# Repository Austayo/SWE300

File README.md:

# SWE300
Silicon Wolf Embedded 300

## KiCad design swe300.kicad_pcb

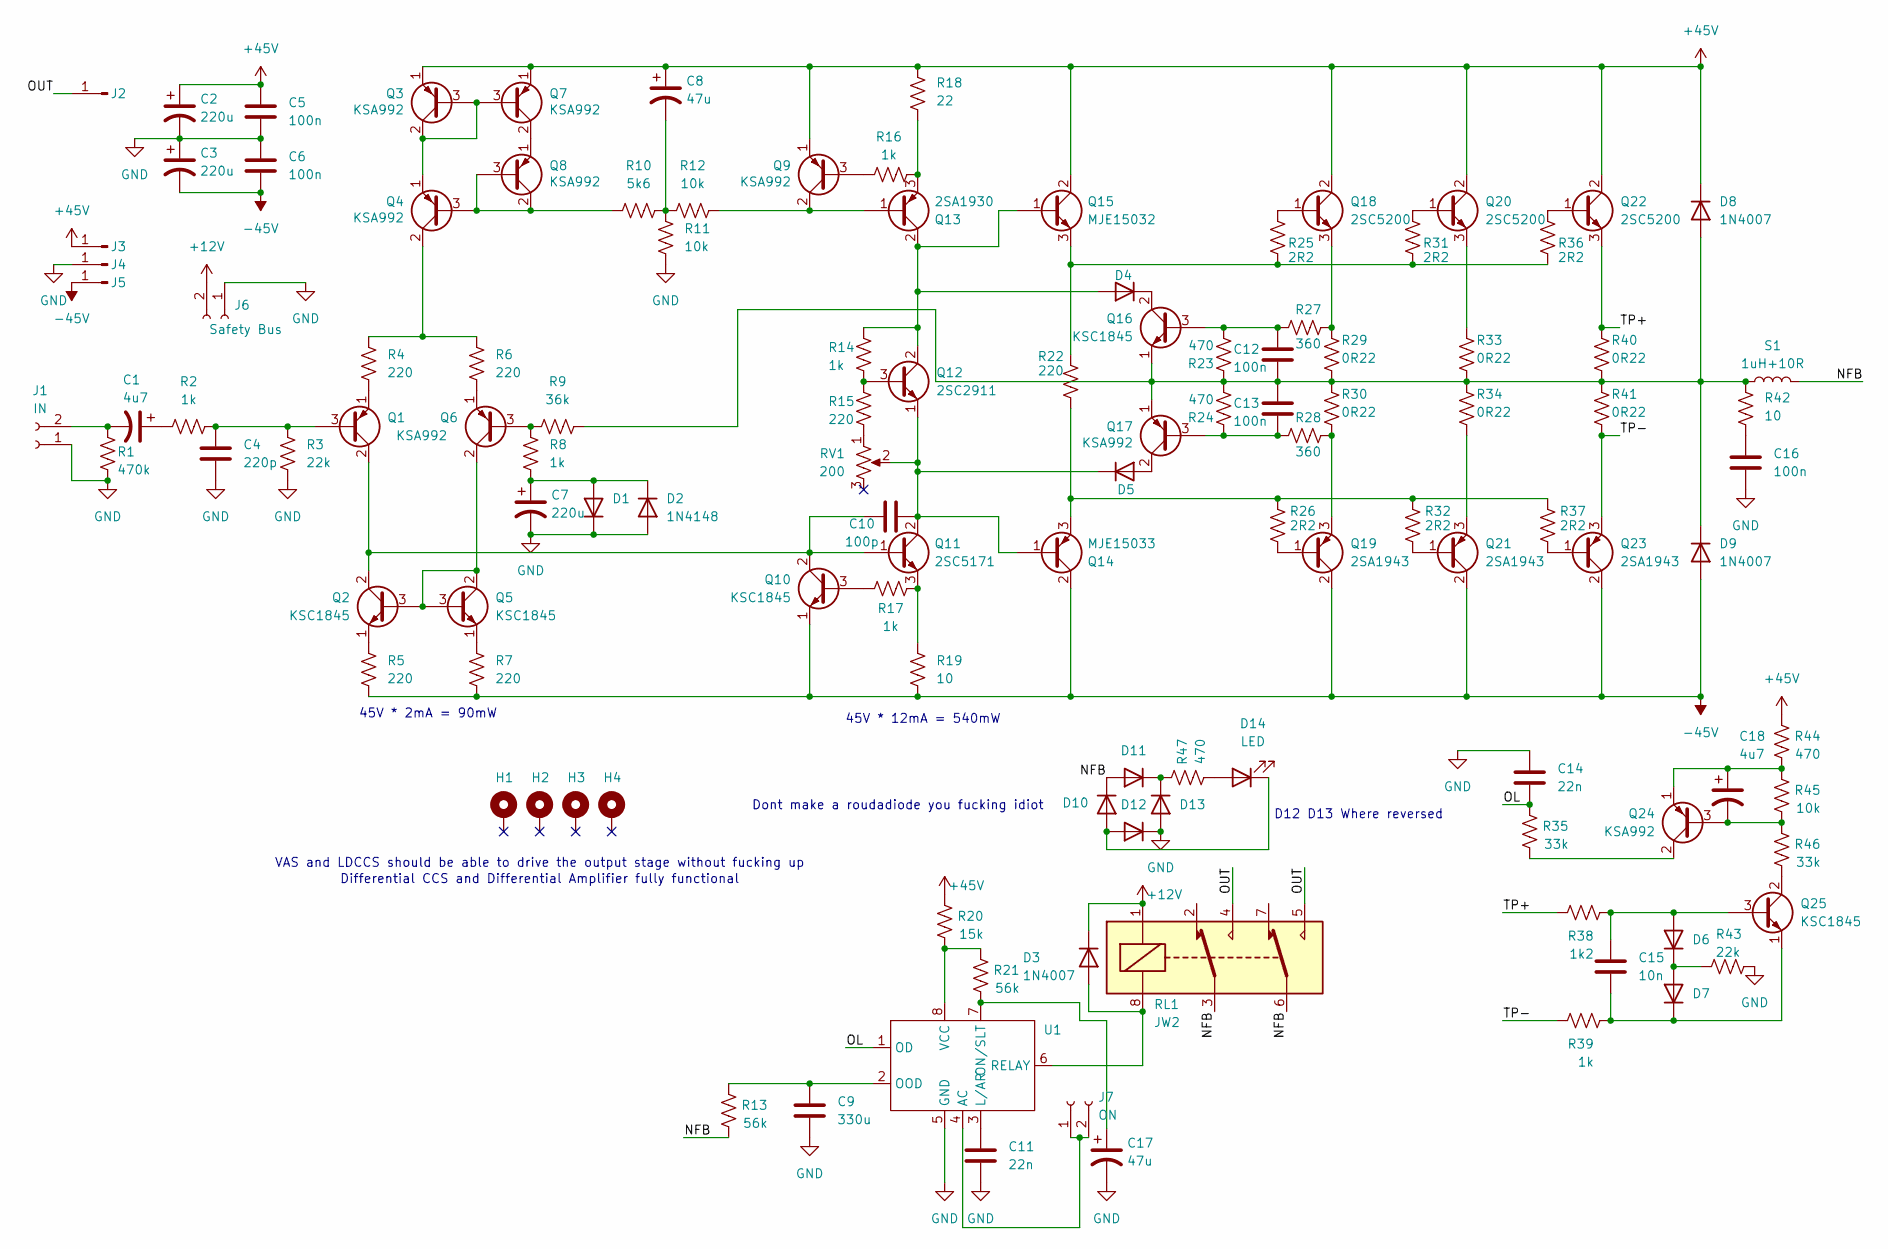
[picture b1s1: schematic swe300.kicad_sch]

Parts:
C1, C18: 4u7; CP_Radial_D6.3mm_P2.50mm
C2, C3: 220u; CP_Radial_D10.0mm_P5.00mm
C4: 220p; C_Disc_D4.7mm_W2.5mm_P5.00mm
C5, C6, C12, C13, C16: 100n; C_Rect_L7.0mm_W2.0mm_P5.00mm
C7: 220u; CP_Radial_D6.3mm_P2.50mm
C8, C17: 47u; CP_Radial_D6.3mm_P2.50mm
C9: 330u; C_Radial_D8.0mm_H11.5mm_P3.50mm
C10: 100p; C_Disc_D4.7mm_W2.5mm_P5.00mm
C11, C14: 22n; C_Rect_L7.0mm_W2.0mm_P5.00mm
C15: 10n; C_Rect_L7.0mm_W2.0mm_P5.00mm
D1, D2, D4, D5, D6, D7, D10, D11, D12, D13: 1N4148; D_DO-35_SOD27_P7.62mm_Horizontal
D3, D8, D9: 1N4007; D_DO-41_SOD81_P10.16mm_Horizontal
D14: LED; LED_D4.0mm
H1, H2, H3, H4: MountingHole_Pad; MountingHole_3.2mm_M3_DIN965_Pad_TopBottom
J1: IN; PinHeader_1x02_P2.54mm_Vertical
J2, J3, J4, J5: 6.3mm spade
J6: Safety Bus; PinHeader_1x02_P2.54mm_Vertical
J7: ON; PinHeader_1x02_P2.54mm_Vertical
Q1, Q3, Q4, Q6, Q7, Q8, Q9, Q17, Q24: KSA992; TO-92L_Inline_Wide
Q2, Q5, Q10, Q16, Q25: KSC1845; TO-92L_Inline_Wide
Q11: 2SC5171; TO-220-3_Vertical
Q12: 2SC2911; TO-126-3_Horizontal_TabUp
Q13: 2SA1930; TO-220-3_Vertical
Q14: MJE15033; TO-220-3_Horizontal_TabUp
Q15: MJE15032; TO-220-3_Horizontal_TabUp
Q18, Q20, Q22: 2SC5200; TO-264-3_Horizontal_TabUp
Q19, Q21, Q23: 2SA1943; TO-264-3_Horizontal_TabUp
R1: 470k; R_Axial_DIN0207_L6.3mm_D2.5mm_P10.16mm_Horizontal
R2, R8, R14, R16, R17, R39: 1k; R_Axial_DIN0207_L6.3mm_D2.5mm_P10.16mm_Horizontal
R3, R43: 22k; R_Axial_DIN0207_L6.3mm_D2.5mm_P10.16mm_Horizontal
R4, R5, R6, R7, R15, R22: 220; R_Axial_DIN0207_L6.3mm_D2.5mm_P10.16mm_Horizontal
R9: 36k; R_Axial_DIN0207_L6.3mm_D2.5mm_P10.16mm_Horizontal
R10: 5k6; R_Axial_DIN0207_L6.3mm_D2.5mm_P10.16mm_Horizontal
R11, R12, R45: 10k; R_Axial_DIN0207_L6.3mm_D2.5mm_P10.16mm_Horizontal
R13, R21: 56k; R_Axial_DIN0207_L6.3mm_D2.5mm_P10.16mm_Horizontal
R18: 22; R_Axial_DIN0207_L6.3mm_D2.5mm_P10.16mm_Horizontal
R19: 10; R_Axial_DIN0207_L6.3mm_D2.5mm_P10.16mm_Horizontal
R20: 15k; R_Axial_DIN0207_L6.3mm_D2.5mm_P10.16mm_Horizontal
R23, R24, R44, R47: 470; R_Axial_DIN0207_L6.3mm_D2.5mm_P10.16mm_Horizontal
R25, R26, R31, R32, R36, R37: 2R2; R_Axial_DIN0207_L6.3mm_D2.5mm_P10.16mm_Horizontal
R27, R28: 360; R_Axial_DIN0207_L6.3mm_D2.5mm_P10.16mm_Horizontal
R29, R30, R33, R34, R40, R41: 0R22; R_Axial_DIN0922_L20.0mm_D9.0mm_P25.40mm_Horizontal
R35, R46: 33k; R_Axial_DIN0207_L6.3mm_D2.5mm_P10.16mm_Horizontal
R38: 1k2; R_Axial_DIN0207_L6.3mm_D2.5mm_P10.16mm_Horizontal
R42: 10; R_Axial_DIN0309_L9.0mm_D3.2mm_P12.70mm_Horizontal
RL1: JW2; Relay_DPDT_Panasonic_JW2
RV1: 200; Potentiometer_Runtron_RM-063_Horizontal
S1: 1uH+10R; 10mm Snubber
U1: SIP-8_19x3mm_P2.54mm

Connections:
+12V: D3.1 (K), J6.2, RL1.1
+45V: C2.1, C5.1, C8.1, D8.1 (K), J3.1, Q3.1 (E), Q7.1 (E), Q9.1 (E), Q15.2 (C), Q18.2 (C), Q20.2 (C), Q22.2 (C), R18.1, R20.1, R44.1
-45V: C3.2, C6.2, D9.2 (A), J5.1, Q10.1 (E), Q14.2 (C), Q19.2 (C), Q21.2 (C), Q23.2 (C), R5.2, R7.2, R19.2
/NFB: D10.1 (K), D11.2 (A), R13.2, RL1.3, RL1.6, S1.2
/OL: C14.2, R35.1, U1.1 (OD)
/OUT: J2.1, RL1.4, RL1.5
/TP+: Q22.3 (E), R38.2, R40.2
/TP-: Q23.3 (E), R39.2, R41.1
GND: C2.2, C3.1, C4.2, C5.2, C6.1, C7.2, C9.2, C11.2, C14.1, C16.2, C17.2, D1.1 (K), D2.2 (A), D12.1 (K), D13.2 (A), J1.1, J4.1, J6.1, R1.2, R3.1, R11.1, R43.2, U1.5 (GND)
unnamed: C1.1, R2.2
unnamed: C8.2, R10.2, R11.2, R12.2
unnamed: C16.1, R42.2
unnamed: C7.1, D1.2 (A), D2.1 (K), R8.1
unnamed: D3.2 (A), RL1.8, U1.6 (RELAY)
unnamed: D4.2 (A), Q12.2 (C), Q13.2 (C), Q15.1 (B), R14.2
unnamed: D4.1 (K), Q16.2 (C)
unnamed: D5.2 (A), Q17.2 (C)
unnamed: C10.2, D5.1 (K), Q11.2 (C), Q12.1 (E), Q14.1 (B), RV1.2
unnamed: C15.1, D6.2 (A), Q25.3 (B), R38.1
unnamed: D6.1 (K), D7.2 (A), R43.1
unnamed: C15.2, D7.1 (K), Q25.1 (E), R39.1
unnamed: C12.1, C13.2, D8.2 (A), D9.1 (K), Q16.1 (E), Q17.1 (E), R9.1, R23.1, R24.2, R29.1, R30.2, R33.1, R34.2, R40.1, R41.2, R42.1, S1.1
unnamed: D10.2 (A), D12.2 (A), D14.1 (K)
unnamed: D11.1 (K), D13.1 (K), R47.1
unnamed: D14.2 (A), R47.2
unnamed: C1.2, J1.2, R1.1
unnamed: J7.1, J7.2, U1.4 (AC)
unnamed: C4.1, Q1.3 (B), R2.1, R3.2
unnamed: C10.1, Q1.2 (C), Q2.2 (C), Q10.2 (C), Q11.1 (B)
unnamed: Q1.1 (E), R4.2
unnamed: Q2.3 (B), Q5.2 (C), Q5.3 (B), Q6.2 (C)
unnamed: Q2.1 (E), R5.1
unnamed: Q3.2 (C), Q3.3 (B), Q4.1 (E), Q7.3 (B)
unnamed: Q4.3 (B), Q8.2 (C), Q8.3 (B), R10.1
unnamed: Q4.2 (C), R4.1, R6.1
unnamed: Q5.1 (E), R7.1
unnamed: Q6.3 (B), R8.2, R9.2
unnamed: Q6.1 (E), R6.2
unnamed: Q7.2 (C), Q8.1 (E)
unnamed: Q9.3 (B), R16.2
unnamed: Q10.3 (B), R17.1
unnamed: Q11.3 (E), R17.2, R19.1
unnamed: Q12.3 (B), R14.1, R15.2
unnamed: Q9.2 (C), Q13.1 (B), R12.1
unnamed: Q13.3 (E), R16.1, R18.2
unnamed: Q14.3 (E), R22.1, R26.2, R32.2, R37.2
unnamed: Q15.3 (E), R22.2, R25.1, R31.1, R36.1
unnamed: C12.2, Q16.3 (B), R23.2, R27.2
unnamed: C13.1, Q17.3 (B), R24.1, R28.2
unnamed: Q18.1 (B), R25.2
unnamed: Q18.3 (E), R27.1, R29.2
unnamed: Q19.1 (B), R26.1
unnamed: Q19.3 (E), R28.1, R30.1
unnamed: Q20.1 (B), R31.2
unnamed: Q20.3 (E), R33.2
unnamed: Q21.1 (B), R32.1
unnamed: Q21.3 (E), R34.1
unnamed: Q22.1 (B), R36.2
unnamed: Q23.1 (B), R37.1
unnamed: C18.2, Q24.3 (B), R45.2, R46.1
unnamed: Q24.2 (C), R35.2
unnamed: C18.1, Q24.1 (E), R44.2, R45.1
unnamed: Q25.2 (C), R46.2
unnamed: R15.1, RV1.1
unnamed: C11.1, U1.3 (L/AR)
unnamed: C17.1, R21.2, U1.7 (ON/SLT)
unnamed: C9.1, R13.1, U1.2 (OOD)
unnamed: R20.2, R21.1, U1.8 (VCC)

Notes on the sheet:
45V * 12mA = 540mW
D12 D13 Where reversed
VAS and LDCCS should be able to drive the output stage without fucking up
45V * 2mA = 90mW
Dont make a roudadiode you fucking idiot
Differential CCS and Differential Amplifier fully functional

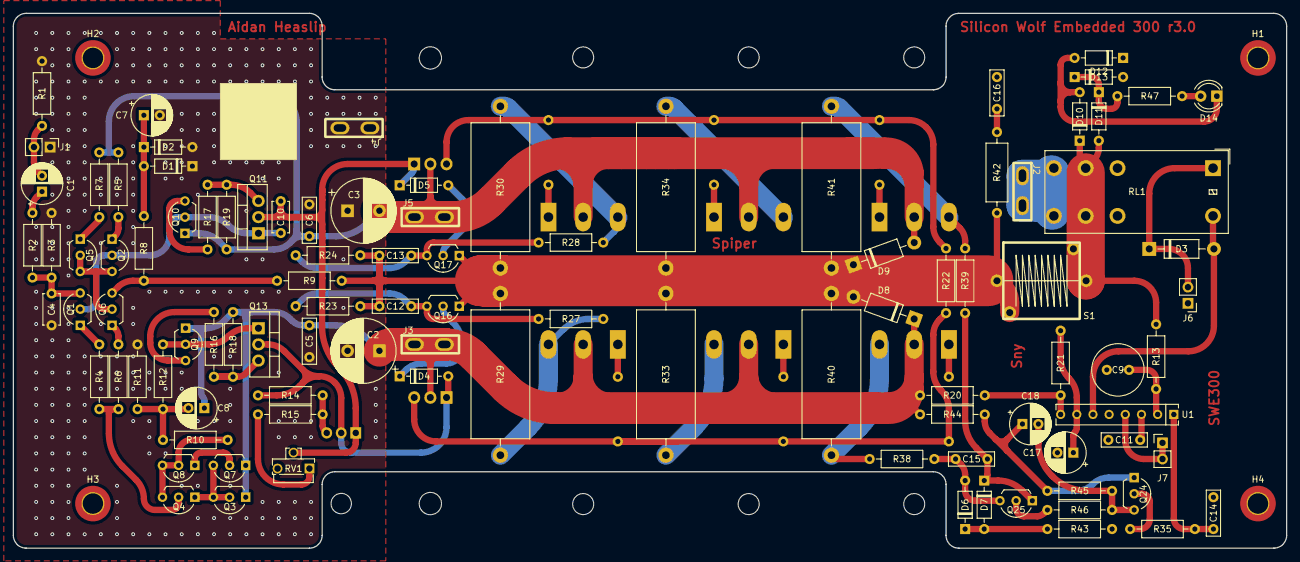
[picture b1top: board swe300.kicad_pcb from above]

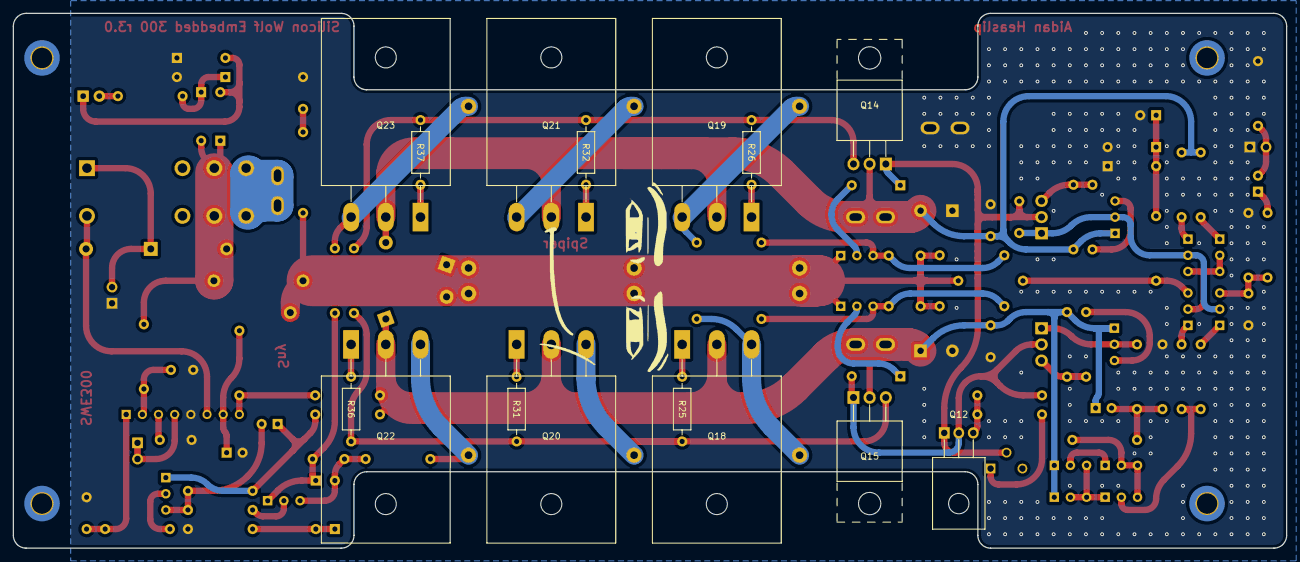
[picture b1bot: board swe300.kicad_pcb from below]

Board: 2 copper layers, 200.0 x 84.0 mm, 119 parts (15 on the bottom side), 68 nets.

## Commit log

2025-03-10 add swe300 files
